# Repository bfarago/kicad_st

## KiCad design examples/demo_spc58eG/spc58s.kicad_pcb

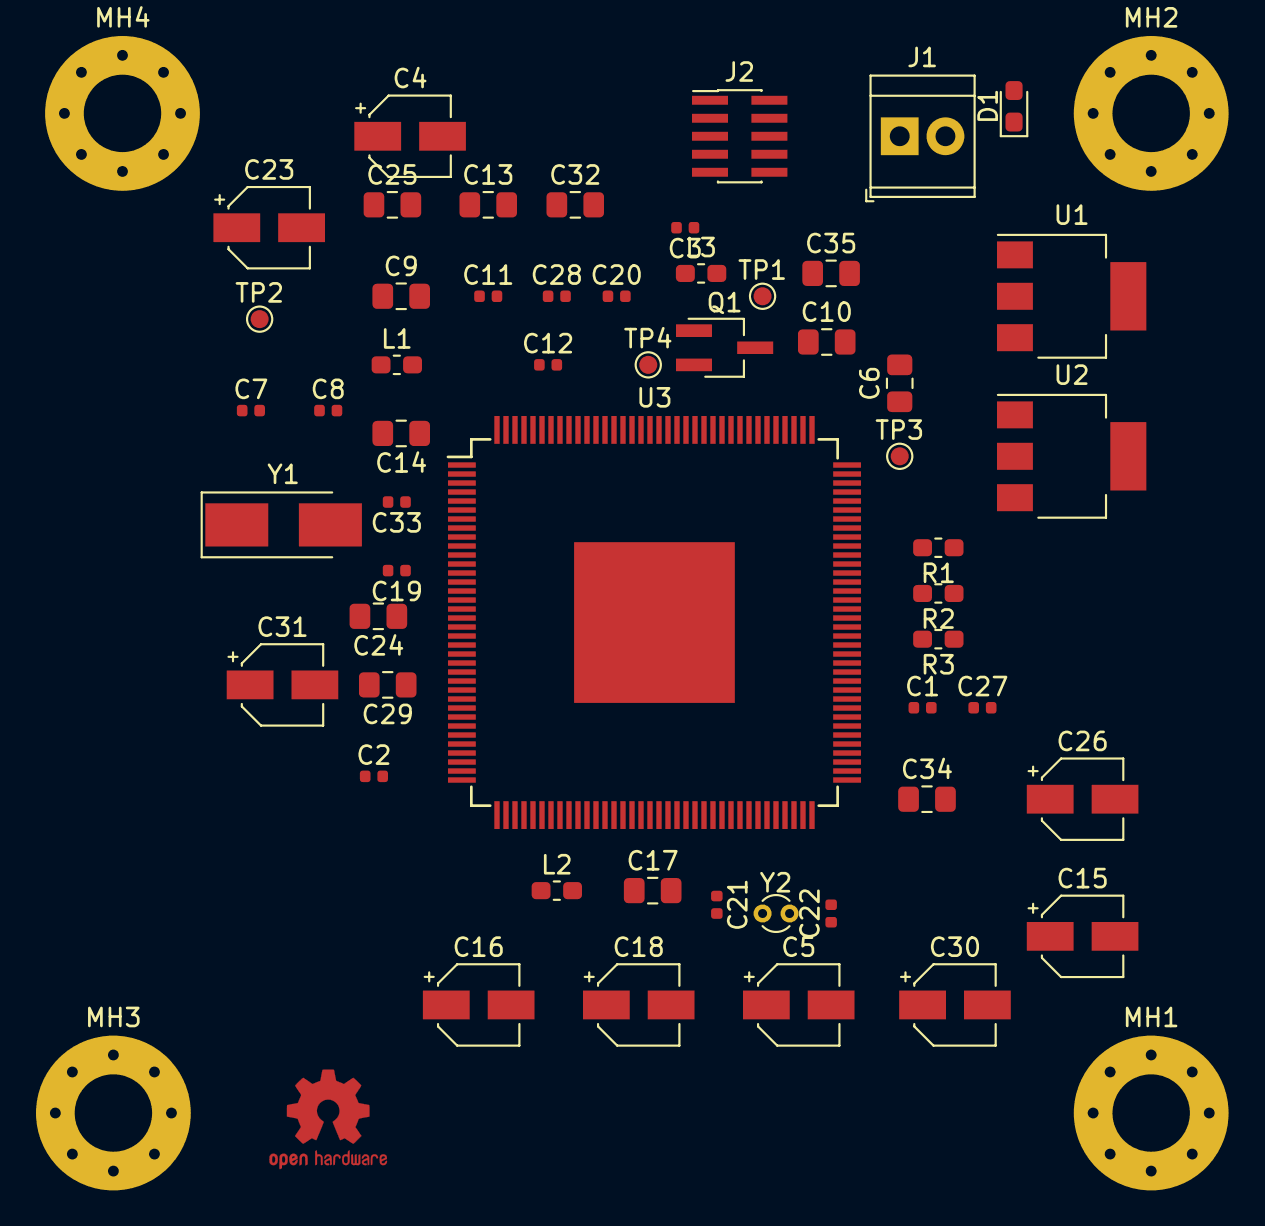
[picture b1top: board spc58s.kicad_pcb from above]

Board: 2 copper layers, 59 parts (0 on the bottom side), 16 nets, no tracks yet.

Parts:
C1, C2, C3, C11, C12, C19, C20, C27, C28, C33: 470p; C_0402_1005Metric
C4, C5, C15, C16, C18, C23, C26, C30, C31: 10u; CP_Elec_4x5.3
C6, C9, C10, C13, C14, C17, C24, C25, C29, C32, C34, C35: 100n; C_0805_2012Metric_Pad1.15x1.40mm_HandSolder
C7, C8, C21, C22: 10p; C_0402_1005Metric
D1: D_Small; D_0603_1608Metric_Pad1.05x0.95mm_HandSolder
J1: Screw_Terminal_01x02; TerminalBlock_TE_282834-2_1x02_P2.54mm_Horizontal
J2: AVR-JTAG-10; PinHeader_2x05_P1.00mm_Vertical_SMD
L1, L2, L3: 26ohm; L_0603_1608Metric_Pad1.05x0.95mm_HandSolder
LOGO1: Logo_Open_Hardware_Small; OSHW-Logo2_7.3x6mm_Copper
MH1, MH2, MH3, MH4: MountingHole_Pad; MountingHole_4.3mm_M4_Pad_Via
Q1: Q_NPN_EBC; SOT-23W_Handsoldering
R1, R2, R3: 4k7; R_0603_1608Metric_Pad1.05x0.95mm_HandSolder
TP1, TP2, TP3, TP4: TestPoint_Pad_D1.0mm
U1: AMS1117-3.3; SOT-223-3_TabPin2
U2: AMS1117-1.5; SOT-223-3_TabPin2
U3: SPC58xG; LQFP-144-1EP_20x20mm_P0.5mm_EP8.93x8.93mm
Y1: 40MHz; Crystal_SMD_5032-2Pin_5.0x3.2mm_HandSoldering
Y2: 32MHz; Crystal_DS10_D1.0mm_L4.3mm_Vertical

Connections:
+1V2: C3.1, C6.1, C11.1, C13.1, C35.1, L3.2, TP2.1, TP3.1, U2.2, U3.22, U3.58, U3.79, U3.99
+3V3: C1.1, C2.1, C4.1, C5.1, C9.1, C10.1, C12.1, C15.1, C17.1, C18.1, C20.1, C23.1, C25.1, C28.1, C30.1, C32.1, C34.1, J2.4, J2.7, L1.1, Q1.3, R1.1, R2.1, R3.1, TP1.1, U1.2, U2.3, U3.23, U3.59, U3.78, U3.83, U3.115, U3.125, U3.136, U3.142
/MainMicro/nRST: R1.2, U3.98
/Power/EXTAL: C8.2, Y1.2
/Power/EXTAL32: C22.2, Y2.2
/Power/XTAL: C7.2, Y1.1
/Power/XTAL32: C21.2, Y2.1
GND: C1.2, C2.2, C3.2, C4.2, C5.2, C6.2, C7.1, C8.1, C9.2, C10.2, C11.2, C12.2, C13.2, C15.2, C17.2, C18.2, C20.2, C21.1, C22.1, C23.2, C25.2, C28.2, C30.2, C32.2, C34.2, C35.2, J1.1, J2.2, J2.10, L2.1, MH1.1, MH2.1, MH3.1, MH4.1, U1.1, U2.1
unnamed: D1.1, U1.3
unnamed: D1.2, J1.2
unnamed: L3.1, Q1.1
unnamed: Q1.2, TP4.1, U3.124
unnamed: R2.2, U3.97
unnamed: R3.2, U3.94
VDDA: C14.1, C16.1, C19.1, C24.1, C26.1, C27.1, C29.1, C31.1, C33.1, L1.2, U3.24, U3.25, U3.42, U3.44
VSSA: C14.2, C16.2, C19.2, C24.2, C26.2, C27.2, C29.2, C31.2, C33.2, L2.2, U3.41, U3.43

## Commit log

2018-10-28 initial version
2018-10-28 add imgage link
2018-10-28 IO def from attachment of en.DM00148989_SPC58_RM0391_rev3
